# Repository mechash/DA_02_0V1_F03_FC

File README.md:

# DA_02_0V1_F03_FC
 Drone FC - Brushed - Freelance Project

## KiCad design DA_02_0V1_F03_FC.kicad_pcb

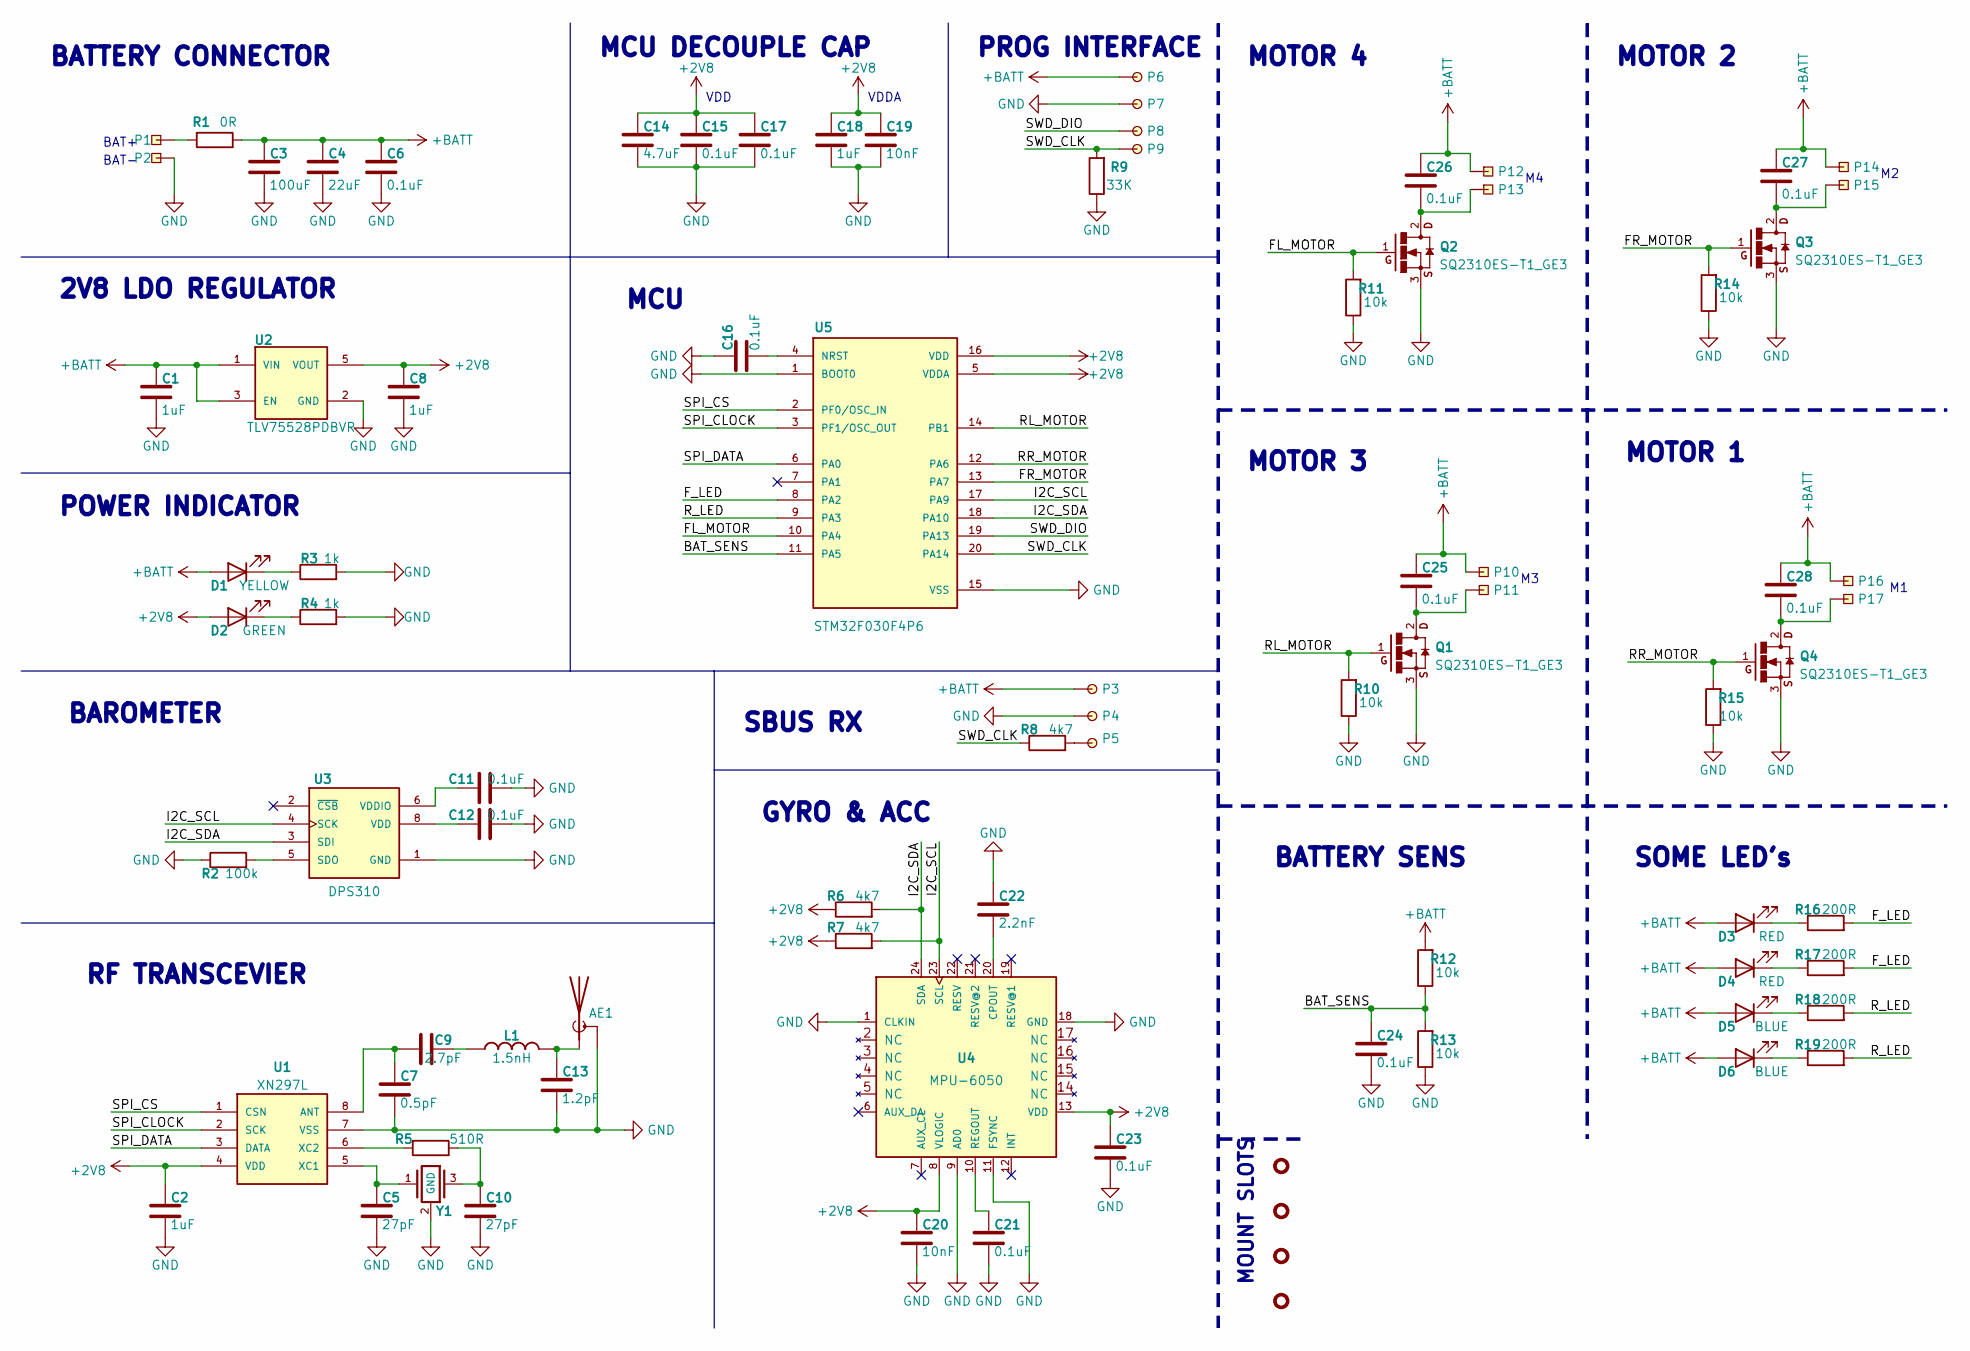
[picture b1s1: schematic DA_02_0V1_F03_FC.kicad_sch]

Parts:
AE1: Antenna_Shield_2.4GHz_R; ANT_Texas_SWRA117D_2.4GHz_Left
C1, C2, C8, C18: 1uF; C_0603; LCSC C113807
C3: 100uF; C_0805; LCSC C141660
C4: 22uF; C_0805; LCSC C77071
C5, C10: 27pF; C_0603; LCSC C107045
C6: 0.1uF; C_0805; LCSC C1854118
C7: 0.5pF; C_0603; LCSC C134255
C9: 2.7pF; C_0603; LCSC C701311
C11, C12, C15, C16, C17, C21, C23, C24: 0.1uF; C_0603; LCSC C519438
C13: 1.2pF; C_0603; LCSC C913582
C14: 4.7uF; C_0603; LCSC C109456
C19, C20: 10nF; C_0603; LCSC C344025
C22: 2.2nF; C_0603; LCSC C519416
C25, C26, C27, C28: 0.1uF; C_0603; LCSC C1854118
D1: YELLOW; LED_0603; LCSC C962599
D2: GREEN; LED_0603; LCSC C4749244
D3, D4: RED; LED_0603; LCSC C266784
D5, D6: BLUE; LED_0603; LCSC C435849
L1: 1.5nH; L_0603; LCSC C22223
M1, M2, M3, M4: M2_Rubber_Gummy_Drone
P1, P2, P10, P11, P12, P13, P14, P15, P16, P17: 2x3_EDGE_PADS
P3, P4, P5, P6, P7, P8, P9: 2x2-SMD_PAD; 1.6x1.6-SMD-PAD
Q1, Q2, Q3, Q4: SQ2310ES-T1_GE3; SOT-23-3; LCSC C145342
R1: 0R; R_0805; LCSC C100045
R2: 100k; R_0603; LCSC C14675
R3, R4: 1k; R_0603; LCSC C14676
R5: 510R; R_0603; LCSC C114670
R6, R7, R8: 4k7; R_0603; LCSC C99782
R9: 33K; R_0603; LCSC C138282
R10, R11, R12, R13, R14, R15: 10k; R_0603; LCSC C98220
R16, R17, R18, R19: 200R; R_0603; LCSC C114664
U1: XN297L; SOP8-EP
U2: TLV75528PDBVR; SOT-23-5; LCSC C2868951
U3: DPS310; VFLGA-8; LCSC C130156
U4: MPU-6050; QFN-24; LCSC C24112
U5: STM32F030F4P6; TSSOP-20; LCSC C32908
Y1: ABM11W-16.0000MHZ; SMD2016-4P; LCSC C2965579

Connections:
+2V8: C2.1, C8.1, C14.1, C15.1, C17.1, C18.1, C19.1, C20.1, C23.1, D2.2 (A), R6.2, R7.2, U1.4 (VDD), U2.5 (VOUT), U4.8 (VLOGIC), U4.13 (VDD), U5.5 (VDDA), U5.16 (VDD)
+BATT: C1.1, C3.1, C4.1, C6.1, C25.1, C26.1, C27.1, C28.1, D1.2 (A), D3.2 (A), D4.2 (A), D5.2 (A), D6.2 (A), P3.1, P6.1, P10.1, P12.1, P14.1, P16.1, R1.2, R12.1, U2.1 (VIN), U2.3 (EN)
/BAT_SENS: C24.1, R12.2, R13.1, U5.11 (PA5)
/FL_MOTOR: Q2.1, R11.1, U5.10 (PA4)
/FR_MOTOR: Q3.1, R14.1, U5.13 (PA7)
/F_LED: R16.1, R17.1, U5.8 (PA2)
/I2C_SCL: R7.1, U3.4 (SCK), U4.23 (SCL), U5.17 (PA9)
/I2C_SDA: R6.1, U3.3 (SDI), U4.24 (SDA), U5.18 (PA10)
/RL_MOTOR: Q1.1, R10.1, U5.14 (PB1)
/RR_MOTOR: Q4.1, R15.1, U5.12 (PA6)
/R_LED: R18.1, R19.1, U5.9 (PA3)
/SPI_CLOCK: U1.2 (SCK), U5.3 (PF1/OSC_OUT)
/SPI_CS: U1.1 (CSN), U5.2 (PF0/OSC_IN)
/SPI_DATA: U1.3 (DATA), U5.6 (PA0)
/SWD_CLK: P9.1, R8.2, R9.1, U5.20 (PA14)
/SWD_DIO: P8.1, U5.19 (PA13)
GND: AE1.2 (Shield), C1.2, C2.2, C3.2, C4.2, C5.2, C6.2, C7.2, C8.2, C10.2, C11.2, C12.2, C13.2, C14.2, C15.2, C16.1, C17.2, C18.2, C19.2, C20.2, C21.2, C22.1, C23.2, C24.2, P2.1, P4.1, P7.1, Q1.3, Q2.3, Q3.3, Q4.3, R2.2, R3.1, R4.1, R9.2, R10.2, R11.2, R13.2, R14.2, R15.2, U1.7 (VSS), U2.2 (GND), U3.1 (GND), U3.7 (GND), U4.1 (CLKIN), U4.9 (AD0), U4.11 (FSYNC), U4.18 (GND), U5.1 (BOOT0), U5.15 (VSS), Y1.2 (GND), Y1.4 (GND)
unnamed: AE1.1 (A), C13.1, L1.2
unnamed: C9.2, L1.1
unnamed: C10.1, R5.2, Y1.3
unnamed: C25.2, P11.1, Q1.2
unnamed: C26.2, P13.1, Q2.2
unnamed: C27.2, P15.1, Q3.2
unnamed: C28.2, P17.1, Q4.2
unnamed: D1.1 (K), R3.2
unnamed: D2.1 (K), R4.2
unnamed: D3.1 (K), R16.2
unnamed: D4.1 (K), R17.2
unnamed: D5.1 (K), R18.2
unnamed: D6.1 (K), R19.2
unnamed: P1.1, R1.1
unnamed: P5.1, R8.1
unnamed: C7.1, C9.1, U1.8 (ANT)
unnamed: C5.1, U1.5 (XC1), Y1.1
unnamed: R5.1, U1.6 (XC2)
unnamed: R2.1, U3.5 (SDO)
unnamed: C12.1, U3.8 (VDD)
unnamed: C11.1, U3.6 (VDDIO)
unnamed: C22.2, U4.20 (CPOUT)
unnamed: C21.1, U4.10 (REGOUT)
unnamed: C16.2, U5.4 (NRST)

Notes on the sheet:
POWER INDICATOR
BAT+
SOME LED's
MCU
BAT-
BATTERY CONNECTOR
MOTOR 3
2V8 LDO REGULATOR
VDDA
BAROMETER
PROG INTERFACE
RF TRANSCEVIER
MOUNT SLOTS
MCU DECOUPLE CAP
SBUS RX
VDD
MOTOR 4
GYRO & ACC
MOTOR 1
BATTERY SENS
MOTOR 2

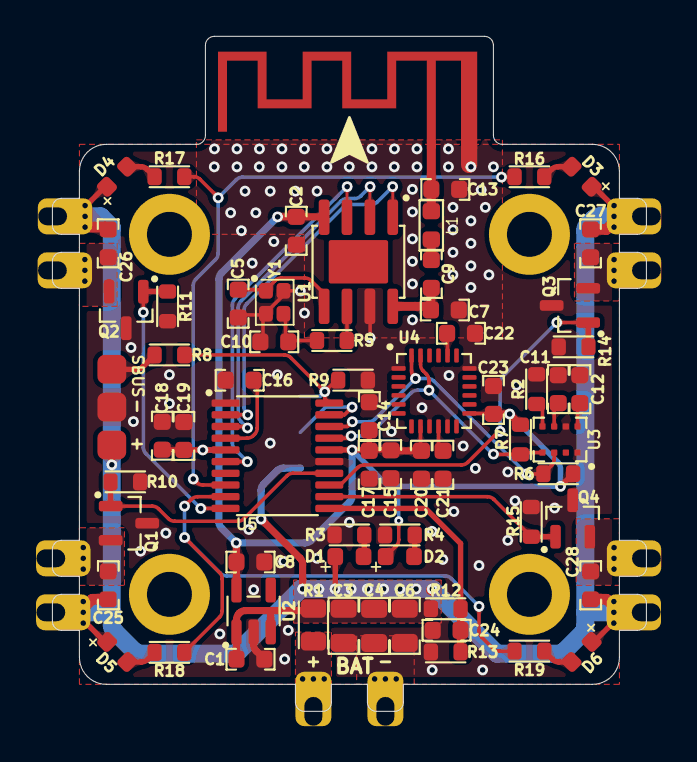
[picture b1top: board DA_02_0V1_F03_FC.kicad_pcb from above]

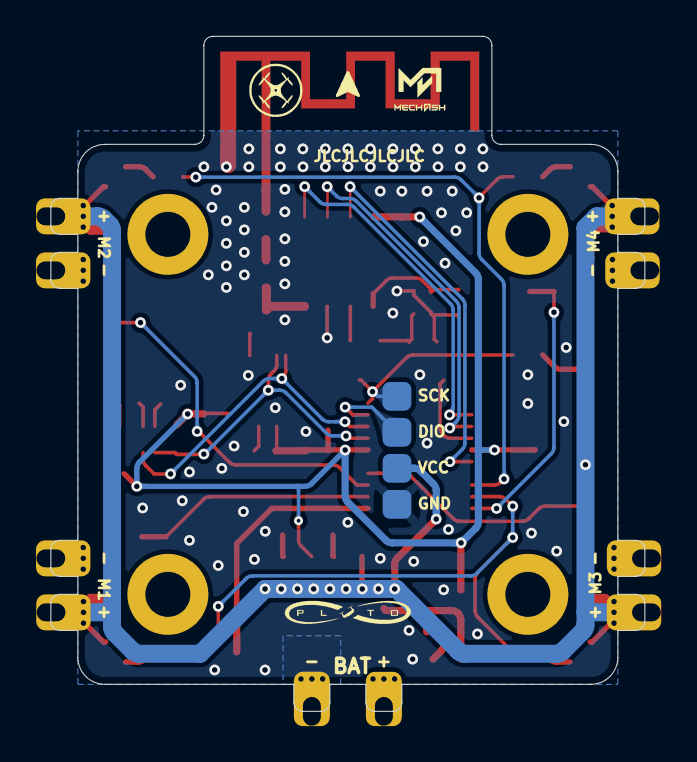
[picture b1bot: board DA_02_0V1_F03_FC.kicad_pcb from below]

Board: 2 copper layers, 33.0 x 37.5 mm, 86 parts (4 on the bottom side), 41 nets.

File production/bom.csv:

Designator,Footprint,Quantity,Value,LCSC Part #
"C1, C18, C2, C8",C_0603,4,1uF,C113807
"C10, C5",C_0603,2,27pF,C107045
"C11, C12, C15, C16, C17, C21, C23, C24, C25, C26, C27, C28",C_0603,12,0.1uF,C519438
C13,C_0603,1,1.2pF,C913582
C14,C_0603,1,4.7uF,C109456
"C19, C20",C_0603,2,10nF,C344025
C22,C_0603,1,2.2nF,C519416
C3,C_0805,1,100uF,C141660
C4,C_0805,1,22uF,C77071
C6,C_0805,1,0.1uF,C1854118
C7,C_0603,1,0.5pF,C134255
C9,C_0603,1,2.7pF,C701311
D1,LED_0603,1,YELLOW ,C962599
D2,LED_0603,1,GREEN,C4749244
"D3, D4",LED_0603,2,RED,C266784
"D5, D6",LED_0603,2,BLUE,C435849
L1,L_0603,1,1.5nH,C22223
"Q1, Q2, Q3, Q4",SOT-23-3,4,SQ2310ES-T1_GE3,C145342
R1,R_0805,1,0R,C100045
"R10, R11, R12, R13, R14, R15",R_0603,6,10k,C98220
"R16, R17, R18, R19",R_0603,4,200R,C114664
R2,R_0603,1,100k,C14675
"R3, R4",R_0603,2,1k,C14676
R5,R_0603,1,510R,C114670
"R6, R7, R8",R_0603,3,4k7,C99782
R9,R_0603,1,33K,C138282
U1,SOP8-EP,1,XN297L,
U2,SOT-23-5,1,TLV75528PDBVR,C2868951
U3,VFLGA-8,1,DPS310,C130156
U4,QFN-24,1,MPU-6050,C24112
U5,TSSOP-20,1,STM32F030F4P6,C32908
Y1,SMD2016-4P,1,ABM11W-16.0000MHZ,C2965579

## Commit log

2023-07-06 Production File
